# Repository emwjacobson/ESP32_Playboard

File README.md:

# ESP32 Playboard

I wasn't sure what to call this project other than the Playboard, so that's what it is. I got really into Espressif's [ESP-IDF](https://idf.espressif.com/) for developing on the ESP32, a dual core system running at 240MHz. The module that I chose has a 16MB SPI Flash chip and 8MB of PSRAM. 8MB and 4MB variants of the WROVER kit are also available, which can slightly reduce the price of it.

Using the LCSC BOM tool, a single board will cost ~$12, reducing to ~$8/board if making 100.

The Playboard includes the following sensors/devices:
- IR LED for Transmitting
- IR Receiver
- MicroSD Card Slot
- MPU-6050 IMU
- SHT30 Temperature/Humidity Sensor

In the PCB I added a small notch between the IR LED and the IR Receiver. This can be used to add a little divider to seperate them if simultaneous operation is required. Without a divider, the LED will be detected by the receiver.

## Schematic

Click to view full size PDF of schematic.

## PCB

## TODO

- JTAG Header
- Add some GPIO LEDs!
- Fill out the README more!

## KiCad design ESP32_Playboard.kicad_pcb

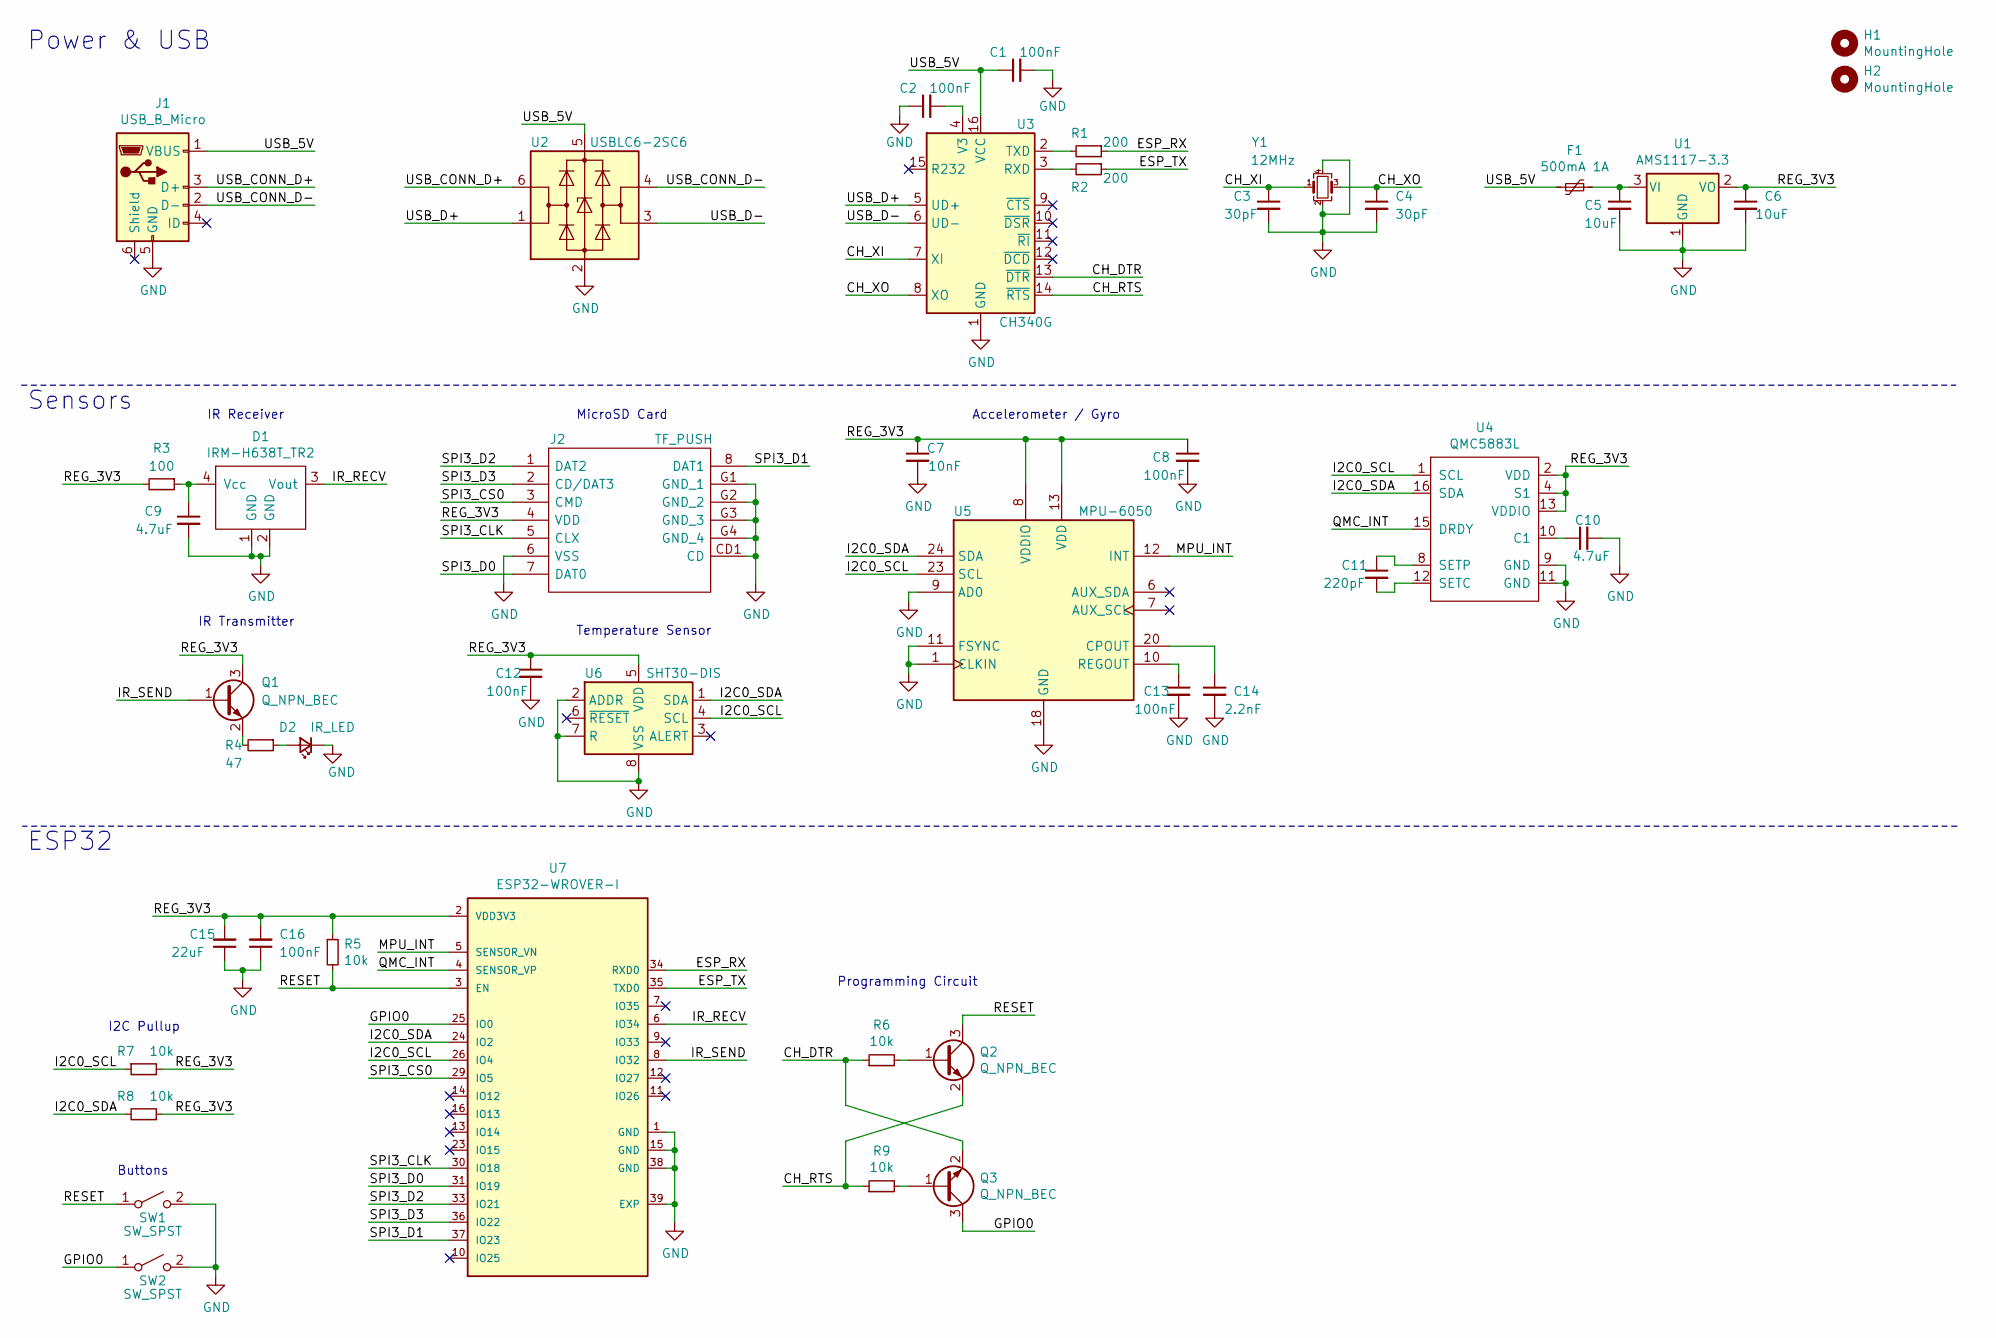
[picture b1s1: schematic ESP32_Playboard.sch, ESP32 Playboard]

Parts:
C1, C2, C8, C12, C13, C16: 100nF; C_0603_1608Metric; Manufacturer Part Number CC0603KRX7R9BB104; LCSC Part Number C14663
C3, C4: 30pF; C_0603_1608Metric; Manufacturer Part Number CC0603FRNPO9BN200; LCSC Part Number C326779
C5, C6: 10uF; C_0603_1608Metric; Manufacturer Part Number CL10A106KP8NNNC; LCSC Part Number C19702
C7: 10nF; C_0603_1608Metric; Manufacturer Part Number 0603B103K500NT; LCSC Part Number C57112
C9, C10: 4.7uF; C_0603_1608Metric; Manufacturer Part Number CL10A475KQ8NNNC; LCSC Part Number C8032
C11: 220pF; C_0603_1608Metric; Manufacturer Part Number CL10C221JB8NNNC; LCSC Part Number C27675
C14: 2.2nF; C_0603_1608Metric; Manufacturer Part Number 0603B222K500NT; LCSC Part Number C1604
C15: 22uF; C_0603_1608Metric; Manufacturer Part Number CL10A226MQ8NRNC; LCSC Part Number C59461
D1: IRM-H638T_TR2; LED-SMD-4; Manufacturer Part Number IRM-H638T/TR2; LCSC Part Number C91447
D2: IR_LED; LED_0603_1608Metric; Manufacturer Part Number MIR60363T; LCSC Part Number C50494
F1: 500mA 1A; Fuse_0805_2012Metric_Castellated; Manufacturer Part Number BSMD0805-050-24V; LCSC Part Number C910822
H1, H2: MountingHole; MountingHole_3.2mm_M3
J1: USB_B_Micro; USB_Micro-B_Amphenol_10118194_Horizontal; Manufacturer Part Number 10118194-0001LF; LCSC Part Number C132563
J2: TF_PUSH; TFPUSH; Manufacturer Part Number TF PUSH; LCSC Part Number C393941
Q1, Q2, Q3: Q_NPN_BEC; SOT-23; Manufacturer Part Number PMBT3904,215; LCSC Part Number C8667
R1, R2: 200; R_0603_1608Metric; Manufacturer Part Number 0603WAJ0201T5E; LCSC Part Number C25217
R3: 100; R_0603_1608Metric; Manufacturer Part Number RC0603FR-07100RL; LCSC Part Number C105588
R4: 47; R_0603_1608Metric; Manufacturer Part Number 0603WAJ0470T5E; LCSC Part Number C1211
R5, R6, R7, R8, R9: 10k; R_0603_1608Metric; Manufacturer Part Number 0603WAF1002T5E; LCSC Part Number C25804
SW1, SW2: SW_SPST; TS-1101-C-W; Manufacturer Part Number TS-1101-C-W; LCSC Part Number C318938
U1: AMS1117-3.3; SOT-223-3_TabPin2; Manufacturer Part Number AMS1117-3.3; LCSC Part Number C347222
U2: USBLC6-2SC6; SOT-23-6; Manufacturer Part Number USBLC6-2SC6; LCSC Part Number C2827654
U3: CH340G; SOIC-16_3.9x9.9mm_P1.27mm; Manufacturer Part Number CH340G; LCSC Part Number C14267
U4: QMC5883L; LGA-16_3x3mm_P0.5mm; Manufacturer Part Number QMC5883L; LCSC Part Number C976032
U5: MPU-6050; InvenSense_QFN-24_4x4mm_P0.5mm; Manufacturer Part Number MPU-6050; LCSC Part Number C24112
U6: SHT30-DIS; Sensirion_DFN-8-1EP_2.5x2.5mm_P0.5mm_EP1.1x1.7mm; Manufacturer Part Number SHT30-DIS-B2.5KS; LCSC Part Number C77361
U7: ESP32-WROVER-I; XCVR_ESP32-WROVER-I; Manufacturer Part Number ESP32-WROVER-IE(16MB); LCSC Part Number C701352
Y1: 12MHz; Crystal_SMD_3225-4Pin_3.2x2.5mm; Manufacturer Part Number X322512MSB4SI; LCSC Part Number C9002

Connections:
/CH_DTR: Q3.2 (E), R6.1, U3.13 (~DTR)
/CH_RTS: Q2.2 (E), R9.1, U3.14 (~RTS)
/CH_XI: C3.1, U3.7 (XI), Y1.1
/CH_XO: C4.1, U3.8 (XO), Y1.3
/ESP_RX: R1.1, U7.34 (RXD0)
/ESP_TX: R2.1, U7.35 (TXD0)
/GPIO0: Q3.3 (C), SW2.1 (A), U7.25 (IO0)
/I2C0_SCL: R7.1, U4.1 (SCL), U5.23 (SCL), U6.4 (SCL), U7.26 (IO4)
/I2C0_SDA: R8.2, U4.16 (SDA), U5.24 (SDA), U6.1 (SDA), U7.24 (IO2)
/IR_RECV: D1.3 (Vout), U7.6 (IO34)
/IR_SEND: Q1.1 (B), U7.8 (IO32)
/MPU_INT: U5.12 (INT), U7.5 (SENSOR_VN)
/QMC_INT: U4.15 (DRDY), U7.4 (SENSOR_VP)
/REG_3V3: C6.1, C7.1, C8.1, C12.1, C15.2, C16.2, J2.4 (VDD), Q1.3 (C), R3.2, R5.1, R7.2, R8.1, U1.2 (VO), U4.2 (VDD), U4.4 (S1), U4.13 (VDDIO), U5.8 (VDDIO), U5.13 (VDD), U6.5 (VDD), U7.2 (VDD3V3)
/RESET: Q2.3 (C), R5.2, SW1.1 (A), U7.3 (EN)
/SPI3_CLK: J2.5 (CLX), U7.30 (IO18)
/SPI3_CS0: J2.3 (CMD), U7.29 (IO5)
/SPI3_D0: J2.7 (DAT0), U7.31 (IO19)
/SPI3_D1: J2.8 (DAT1), U7.37 (IO23)
/SPI3_D2: J2.1 (DAT2), U7.33 (IO21)
/SPI3_D3: J2.2 (CD/DAT3), U7.36 (IO22)
/USB_5V: C1.1, F1.2, J1.1 (VBUS), U2.5 (VBUS), U3.16 (VCC)
/USB_CONN_D+: J1.3 (D+), U2.6 (I/O1)
/USB_CONN_D-: J1.2 (D-), U2.4 (I/O2)
/USB_D+: U2.1 (I/O1), U3.5 (UD+)
/USB_D-: U2.3 (I/O2), U3.6 (UD-)
GND: C1.2, C2.1, C3.2, C4.2, C5.2, C6.2, C7.2, C8.2, C9.2, C10.2, C12.2, C13.2, C14.2, C15.1, C16.1, D1.1 (GND), D1.2 (GND), D2.1 (K), J1.5 (GND), J2.6 (VSS), J2.CD1 (CD), J2.G1 (GND_1), J2.G2 (GND_2), J2.G3 (GND_3), J2.G4 (GND_4), SW1.2 (B), SW2.2 (B), U1.1 (GND), U2.2 (GND), U3.1 (GND), U4.9 (GND), U4.11 (GND), U5.1 (CLKIN), U5.9 (AD0), U5.11 (FSYNC), U5.18 (GND), U6.2 (ADDR), U6.7 (R), U6.8 (VSS), U6.9 (VSS), U7.1 (GND), U7.15 (GND), U7.38 (GND), U7.39 (EXP), Y1.2, Y1.4
unnamed: C2.2, U3.4 (V3)
unnamed: C5.1, F1.1, U1.3 (VI)
unnamed: C9.1, D1.4 (Vcc), R3.1
unnamed: C10.1, U4.10 (C1)
unnamed: C11.1, U4.8 (SETP)
unnamed: C11.2, U4.12 (SETC)
unnamed: C13.1, U5.10 (REGOUT)
unnamed: C14.1, U5.20 (CPOUT)
unnamed: D2.2 (A), R4.1
unnamed: Q1.2 (E), R4.2
unnamed: Q2.1 (B), R6.2
unnamed: Q3.1 (B), R9.2
unnamed: R1.2, U3.2 (TXD)
unnamed: R2.2, U3.3 (RXD)

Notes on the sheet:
Power & USB
ESP32
Sensors
IR Receiver
IR Transmitter
MicroSD Card
Temperature Sensor
Programming Circuit
I2C Pullup
Buttons
Accelerometer / Gyro

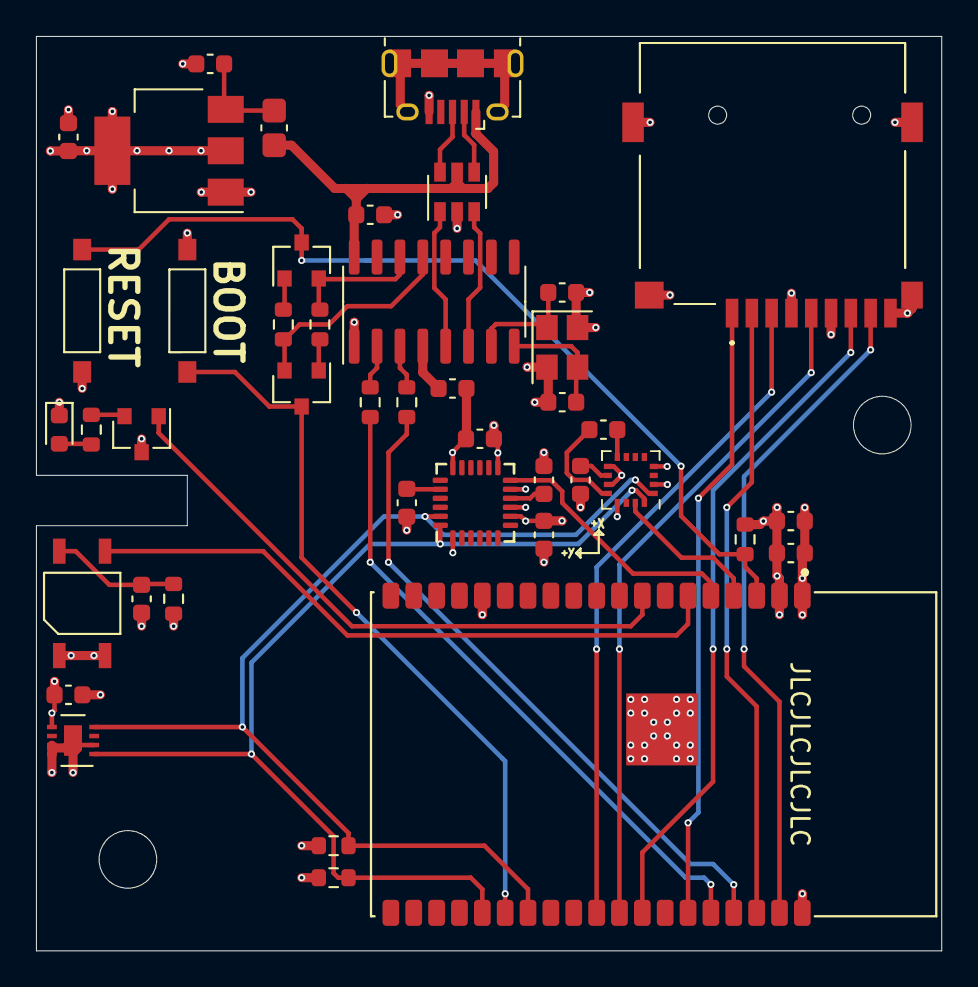
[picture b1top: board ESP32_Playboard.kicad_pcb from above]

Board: 4 copper layers, 50.3 x 50.8 mm, 45 parts (0 on the bottom side), 41 nets.

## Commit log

2021-12-17 Added IR Transmitter & Receiver
2021-12-17 Finished adding SD Card, IMU, Temp sensor
2021-12-17 Started work on PCB
2021-12-17 Worked more on PCB layout
2021-12-18 Finished majority of PCB design
2021-12-18 Finished PCB design
2021-12-18 Began work converting to esp module
2021-12-18 Updated schematic to include wrover module
2021-12-18 Finished basic PCB layout (no routing)
2021-12-18 Finished PCB layout
2021-12-19 Exported Gerber and started Readme
2021-12-19 Added 3d models to missing components
2021-12-19 Rearranged the schematic
2021-12-19 Updated schematic and pcb images
2021-12-19 Added magnetometer, attached interrupts, added silkscreen orientation
